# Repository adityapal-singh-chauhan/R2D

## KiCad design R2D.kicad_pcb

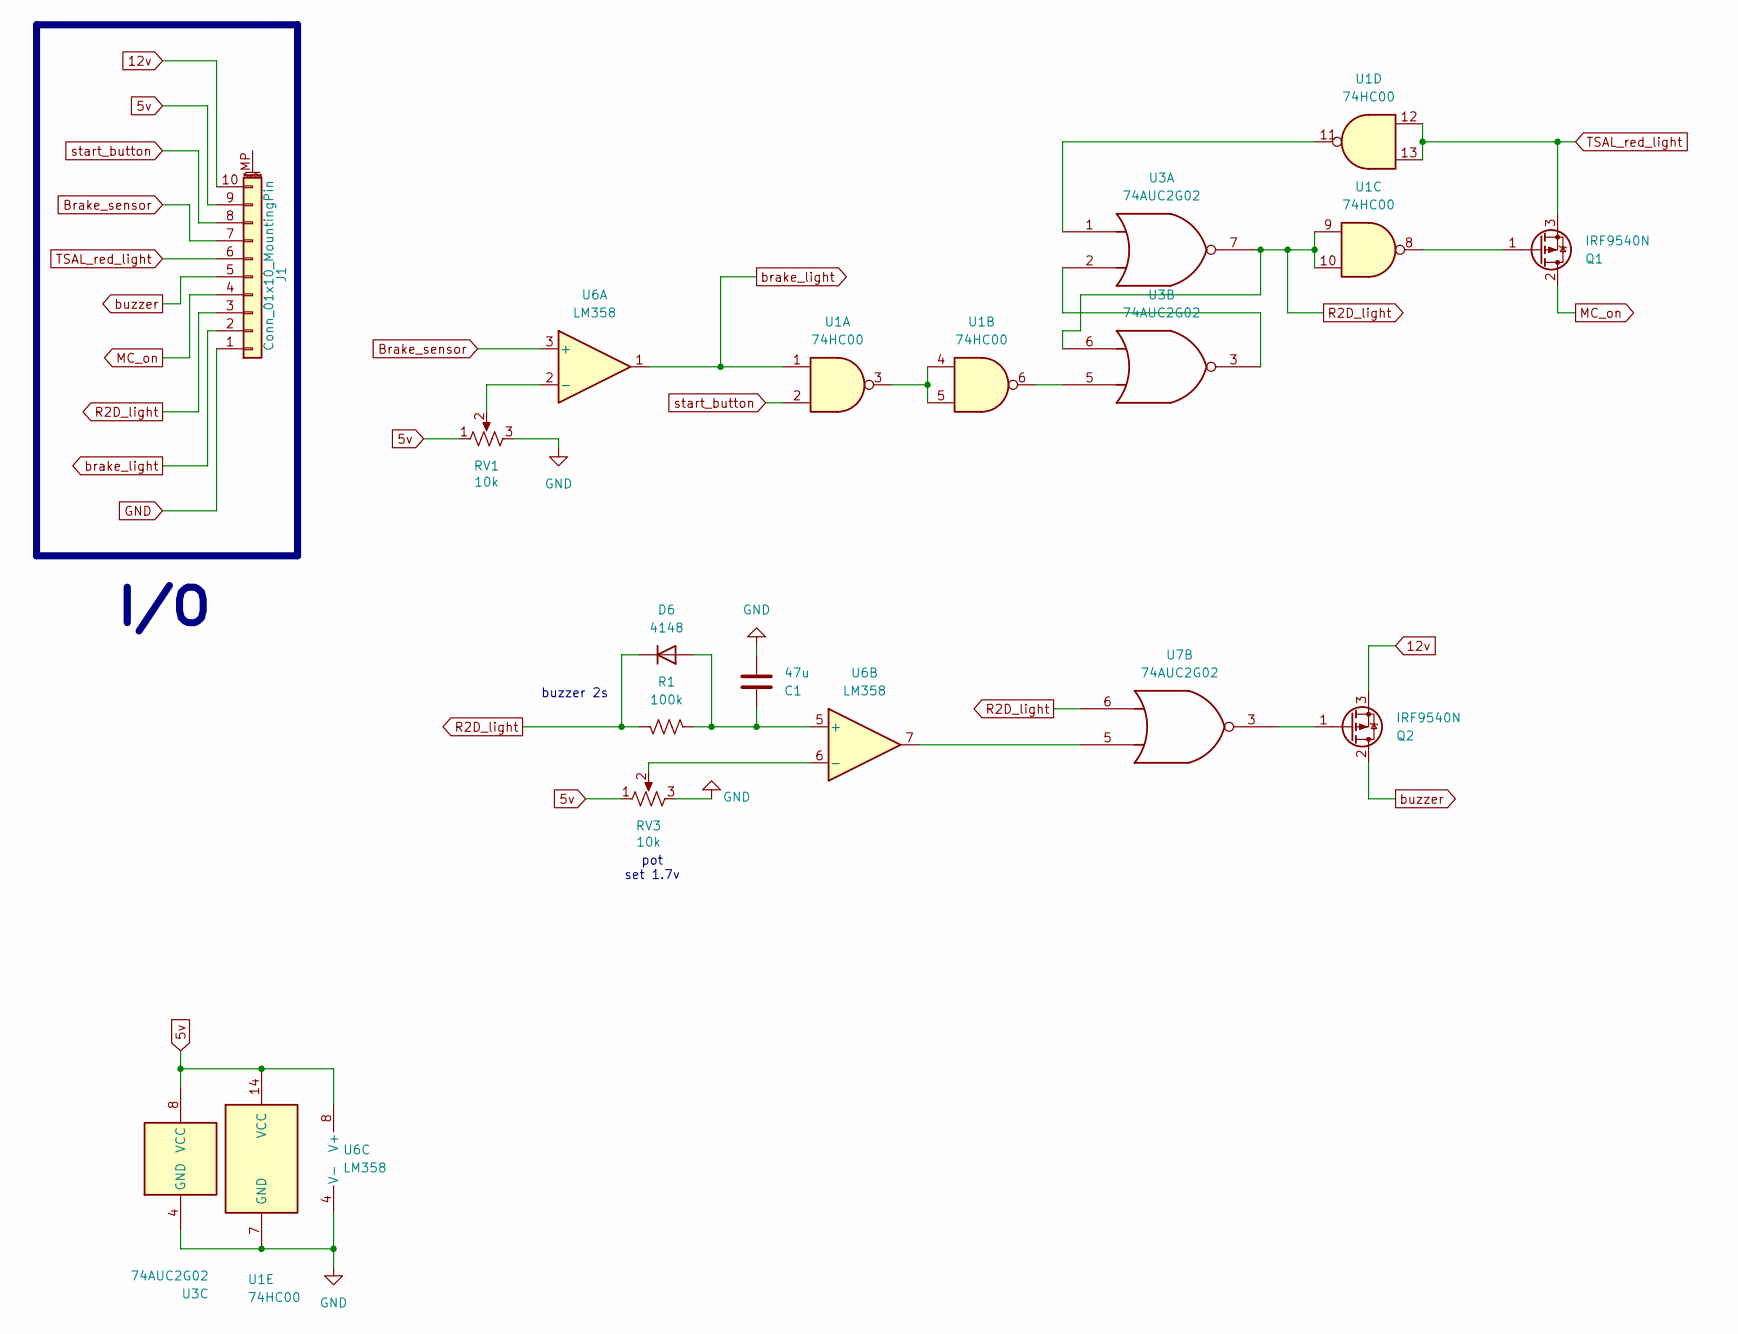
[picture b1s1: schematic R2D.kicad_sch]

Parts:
C1: 47u; CP_Radial_D4.0mm_P2.00mm
D6: 4148; D_DO-41_SOD81_P7.62mm_Horizontal
J1: Conn_01x10_MountingPin; PinHeader_1x10_P2.54mm_Vertical
Q1, Q2: IRF9540N; TO-220-3_Vertical
R1: 100k; R_Axial_DIN0204_L3.6mm_D1.6mm_P7.62mm_Horizontal
RV1, RV3: 10k; Potentiometer_Bourns_3339H_Vertical
U1: 74HC00; DIP-14_W7.62mm
U3: 74AUC2G02
U6: LM358; DIP-8_W7.62mm_Socket
U7: 74AUC2G02; DIP-14_W7.62mm

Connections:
5v: J1.9, RV1.1, RV3.1, U1.14 (VCC), U3.8 (VCC), U6.8 (V+)
12v: J1.10, Q2.3 (S)
Brake_sensor: J1.7, U6.3 (+)
GND: C1.2, J1.1, RV1.3, RV3.3, U1.7 (GND), U3.4 (GND), U6.4 (V-)
MC_on: J1.4, Q1.2 (D)
unnamed: C1.1, D6.2 (A), R1.1, U6.5 (+)
unnamed: Q1.1 (G), U1.8
unnamed: Q2.1 (G), U7.3
unnamed: U1.3, U1.4, U1.5
unnamed: U1.6, U3.5
unnamed: U1.11, U3.1
unnamed: U3.2, U3.3
unnamed: U6.7, U7.5
unnamed: RV1.2, U6.2 (-)
unnamed: RV3.2, U6.6 (-)
R2D_light: D6.1 (K), J1.3, R1.2, U1.9, U1.10, U3.6, U3.7, U7.6
TSAL_red_light: J1.6, Q1.3 (S), U1.12, U1.13
brake_light: J1.2, U1.1, U6.1
buzzer: J1.5, Q2.2 (D)
start_button: J1.8, U1.2

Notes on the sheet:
pot set 1.7v
I/O
buzzer 2s

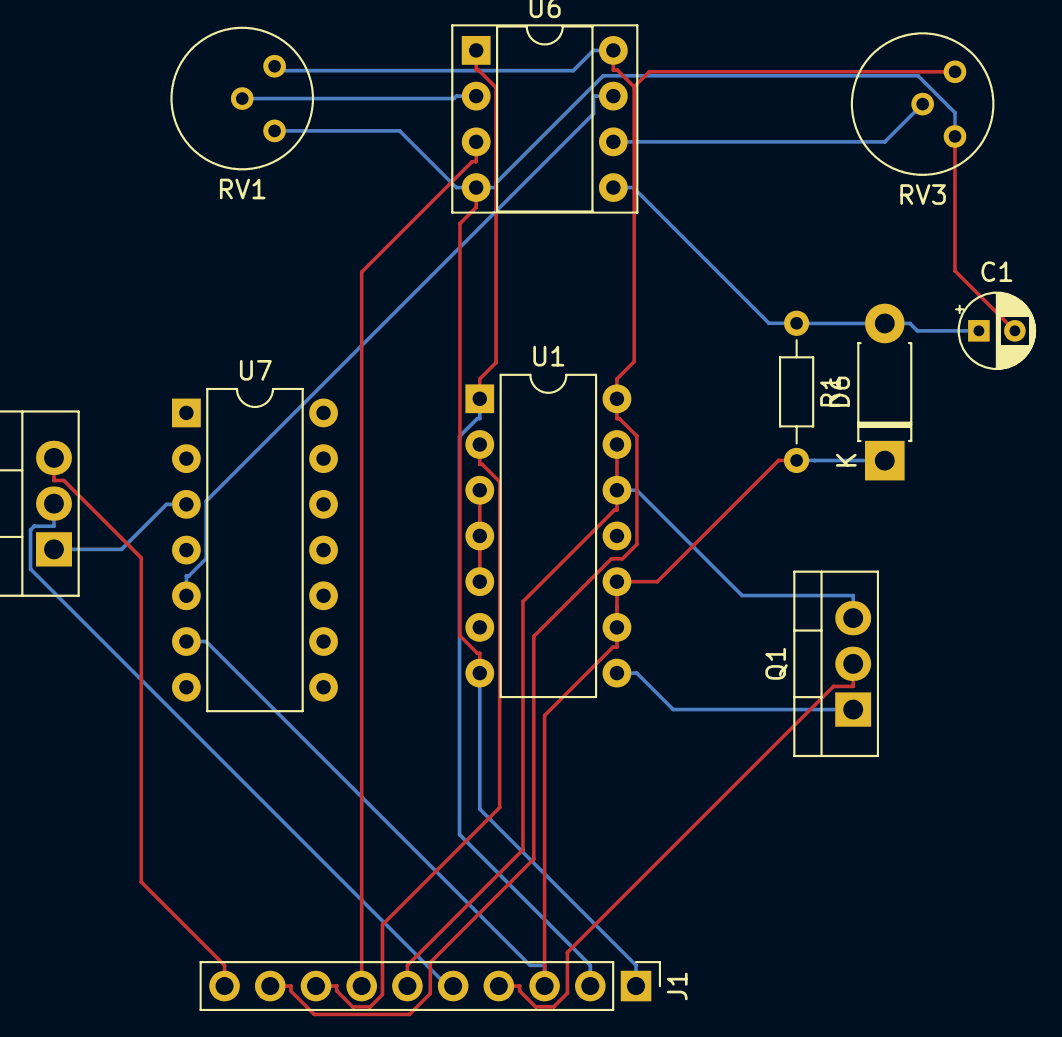
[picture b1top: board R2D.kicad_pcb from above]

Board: 2 copper layers, 11 parts (0 on the bottom side), 17 nets.
